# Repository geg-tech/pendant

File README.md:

# pendant
my #pendant submission for hack club! based off the arcane potion from defend the statue np <br/>
> "wtf is defend the statue" you may ask <br/>
> its a roblox game! its really fun! play it! play it! play it! [now!](https://www.roblox.com/games/6911596531/Defend-the-Statue)
> i have like 160 hours in ts

this keychain lights up in rgb colors and changes colors depending if you shake it or not, powered all by a seeed esp32! <br/>

## schematic
 <br/>
> enjoy dumbfounded soup <br/>

## pcb
 <br/>
 <br/>
 <br/>

## cad n case n stuff
 <br/>
 <br/>
 <br/>
 <br/>

## bom
find it [here](https://github.com/geg-tech/pendant/blob/main/pendant%20BOM%20-%20Sheet1.csv)! (or just go to the bom shaped .csv file in this repo right above ya)

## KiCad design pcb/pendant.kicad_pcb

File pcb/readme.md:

# pcb stuff
find the source files n stuff here + production <br/>
> its a 2 for 1 deal! <br/>

 <br/>
 <br/>

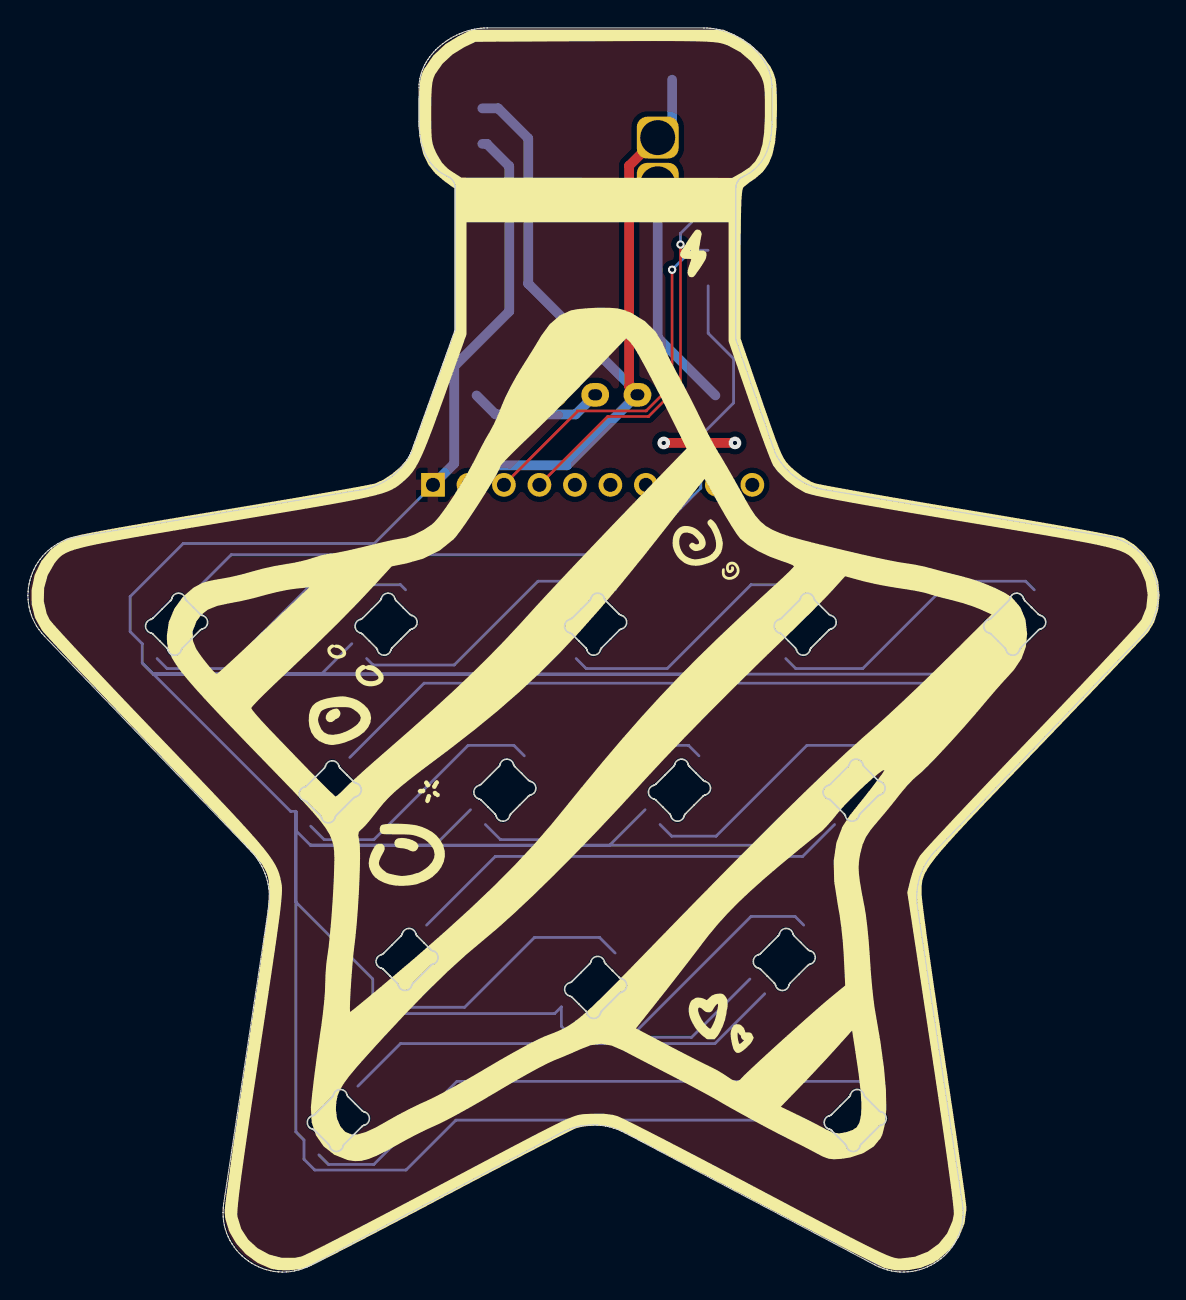
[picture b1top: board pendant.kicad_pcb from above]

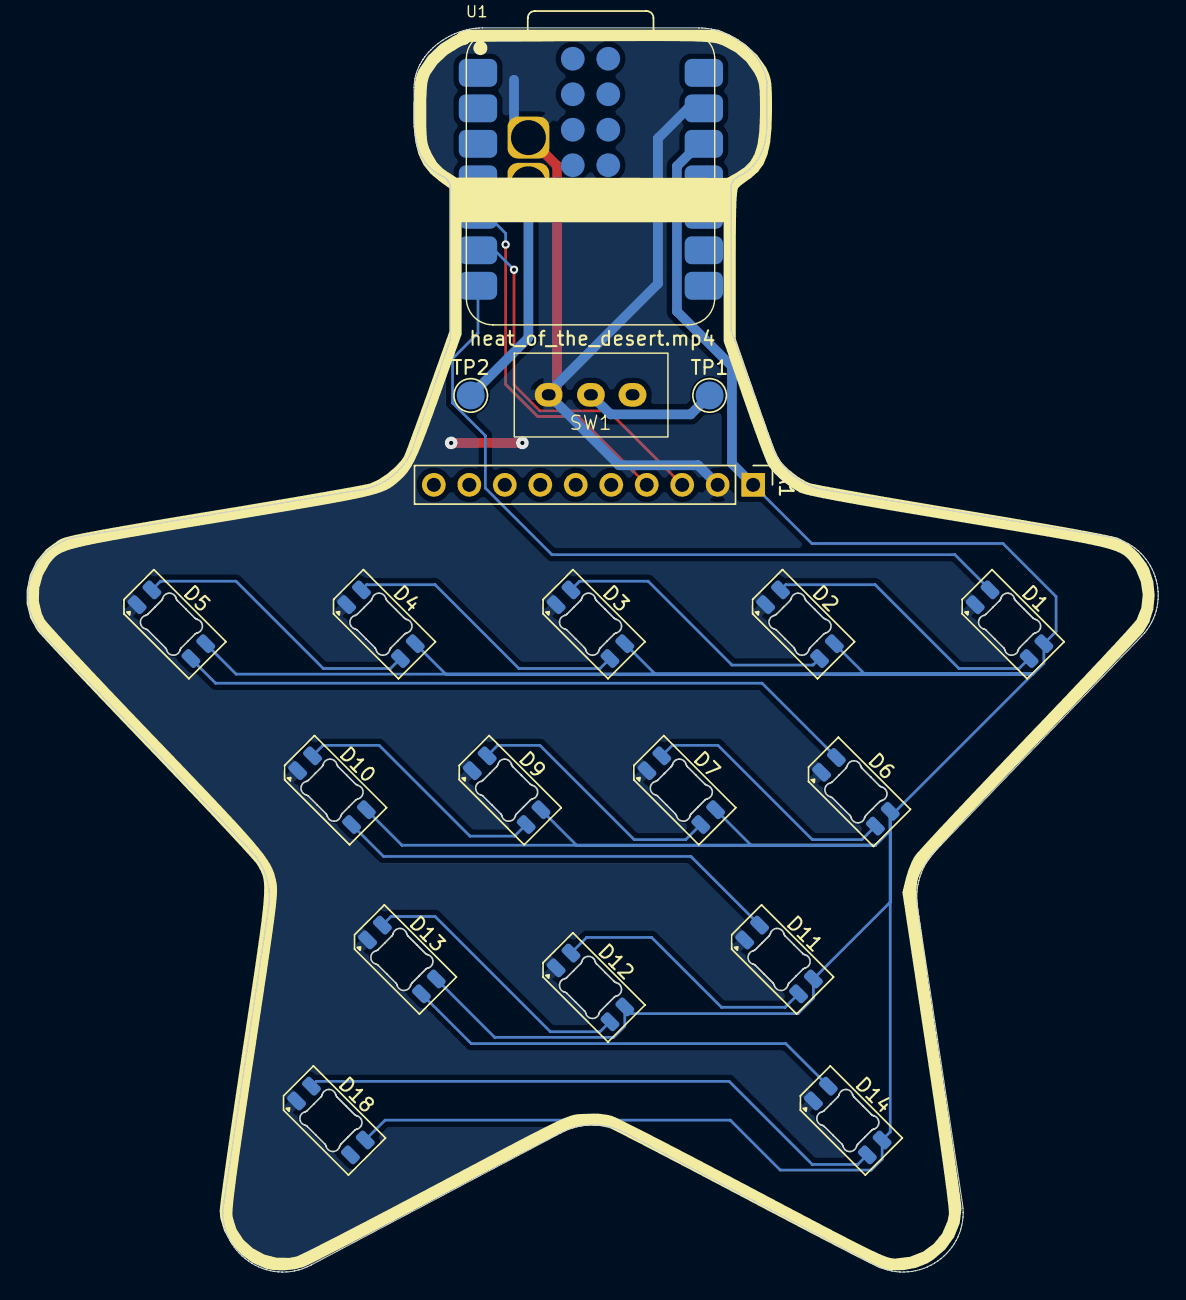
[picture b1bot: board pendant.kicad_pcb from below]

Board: 2 copper layers, 80.9 x 89.1 mm, 19 parts (19 on the bottom side), 20 nets.

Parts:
A1: PinHeader_1x10_P2.54mm_Vertical
D1, D2, D3, D4, D5, D6, D7, D9, D10, D11, D12, D13, D14, D18: SK6812MINI-E; LED_SK6812MINI-E_3.2x2.8mm_P1.5mm_ReverseMount
SW1: SW_SPDT; slideswitch
TP1: GND test Point; TestPoint_Pad_D2.0mm
TP2: BAT Test Point; TestPoint_Pad_D2.0mm
U1: XIAO-ESP32-S3-SMD; XIAO-ESP32S3-SMD

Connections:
+3V3: A1.1, D1.3 (VDD), D2.3 (VDD), D3.3 (VDD), D4.3 (VDD), D5.3 (VDD), D6.3 (VDD), D7.3 (VDD), D9.3 (VDD), D10.3 (VDD), D11.3 (VDD), D12.3 (VDD), D13.3 (VDD), D14.3 (VDD), D18.3 (VDD), U1.12 (3V3)
GND: A1.2, D1.1 (VSS), D2.1 (VSS), D3.1 (VSS), D4.1 (VSS), D5.1 (VSS), D6.1 (VSS), D7.1 (VSS), D9.1 (VSS), D10.1 (VSS), D11.1 (VSS), D12.1 (VSS), D13.1 (VSS), D14.1 (VSS), D18.1 (VSS), SW1.1 (A), U1.13 (GND), U1.16 (GND)
LED: D1.2 (DIN), U1.7 (GPIO43_A6_D6_TX)
unnamed: D1.4 (DOUT), D2.2 (DIN)
unnamed: D2.4 (DOUT), D3.2 (DIN)
unnamed: D3.4 (DOUT), D4.2 (DIN)
unnamed: D4.4 (DOUT), D5.2 (DIN)
unnamed: D5.4 (DOUT), D6.2 (DIN)
unnamed: D6.4 (DOUT), D7.2 (DIN)
unnamed: D7.4 (DOUT), D9.2 (DIN)
unnamed: D9.4 (DOUT), D10.2 (DIN)
unnamed: D10.4 (DOUT), D11.2 (DIN)
unnamed: D11.4 (DOUT), D12.2 (DIN)
unnamed: D12.4 (DOUT), D13.2 (DIN)
unnamed: D13.4 (DOUT), D14.2 (DIN)
unnamed: D14.4 (DOUT), D18.2 (DIN)
unnamed: SW1.1 (A), TP1.1 (1_1)
SCL: A1.3, U1.6 (GPIO6_A5_D5_SCL)
SDA: A1.4, U1.5 (GPIO5_A4_D4_SDA)
VBAT: TP2.1 (1_1), U1.15 (BAT)

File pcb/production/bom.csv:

Designator,Footprint,Quantity,Value,LCSC Part #
A1,PinHeader_1x10_P2.54mm_Vertical,1,~,
"D1, D10, D11, D12, D13, D14, D18, D2, D3, D4, D5, D6, D7, D9",LED_SK6812MINI-E_3.2x2.8mm_P1.5mm_ReverseMount,14,SK6812MINI-E,
SW1,slideswitch,1,SW_SPDT,
TP1,TestPoint_Pad_D2.0mm,1,GND test Point,
TP2,TestPoint_Pad_D2.0mm,1,BAT Test Point,
U1,XIAO-ESP32S3-SMD,1,XIAO-ESP32-S3-SMD,

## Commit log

2026-06-18 Correct date format in journal entry
2026-06-18 Update journal with new ideas and outlines
    Added new entry for idea generation and outlines.
2026-06-18 saving
2026-06-19 Create README for CAD project
    Added a README file with a welcome message and image.
2026-06-19 Update readme with game and wiki links
